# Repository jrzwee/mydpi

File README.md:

# mydpi
OpenSource debugger and programmer for ATmega and ATtiny microcontrollers from Microchip.

## Usage
+ Connect the myDPI to your computer, it should be recognised automatically. 
+ In Atmel Studio choose the myDPI debugger.
+ Set brakepoints, start debugging.

The connection to the device is realised with a Wurth Electronics [REDFIT](https://www.we-online.com/web/en/electronic_components/produkte_pb/produktinnovationen/redfit.php)
connector.

## Compatible Microcontrollers
+ ATtiny20x/40x/80x/160x
+ ATtiny21x/41x/81x/161x/321x
+ ATmega80x/160x/320x/480x

## Manufacture PCB
Click the logo to preview the order "**Push to Aisler**":

If you like this project, feel free to support me 😇

## License
[CERN-OHL-S](https://ohwr.org/cern_ohl_s_v2.pdf)

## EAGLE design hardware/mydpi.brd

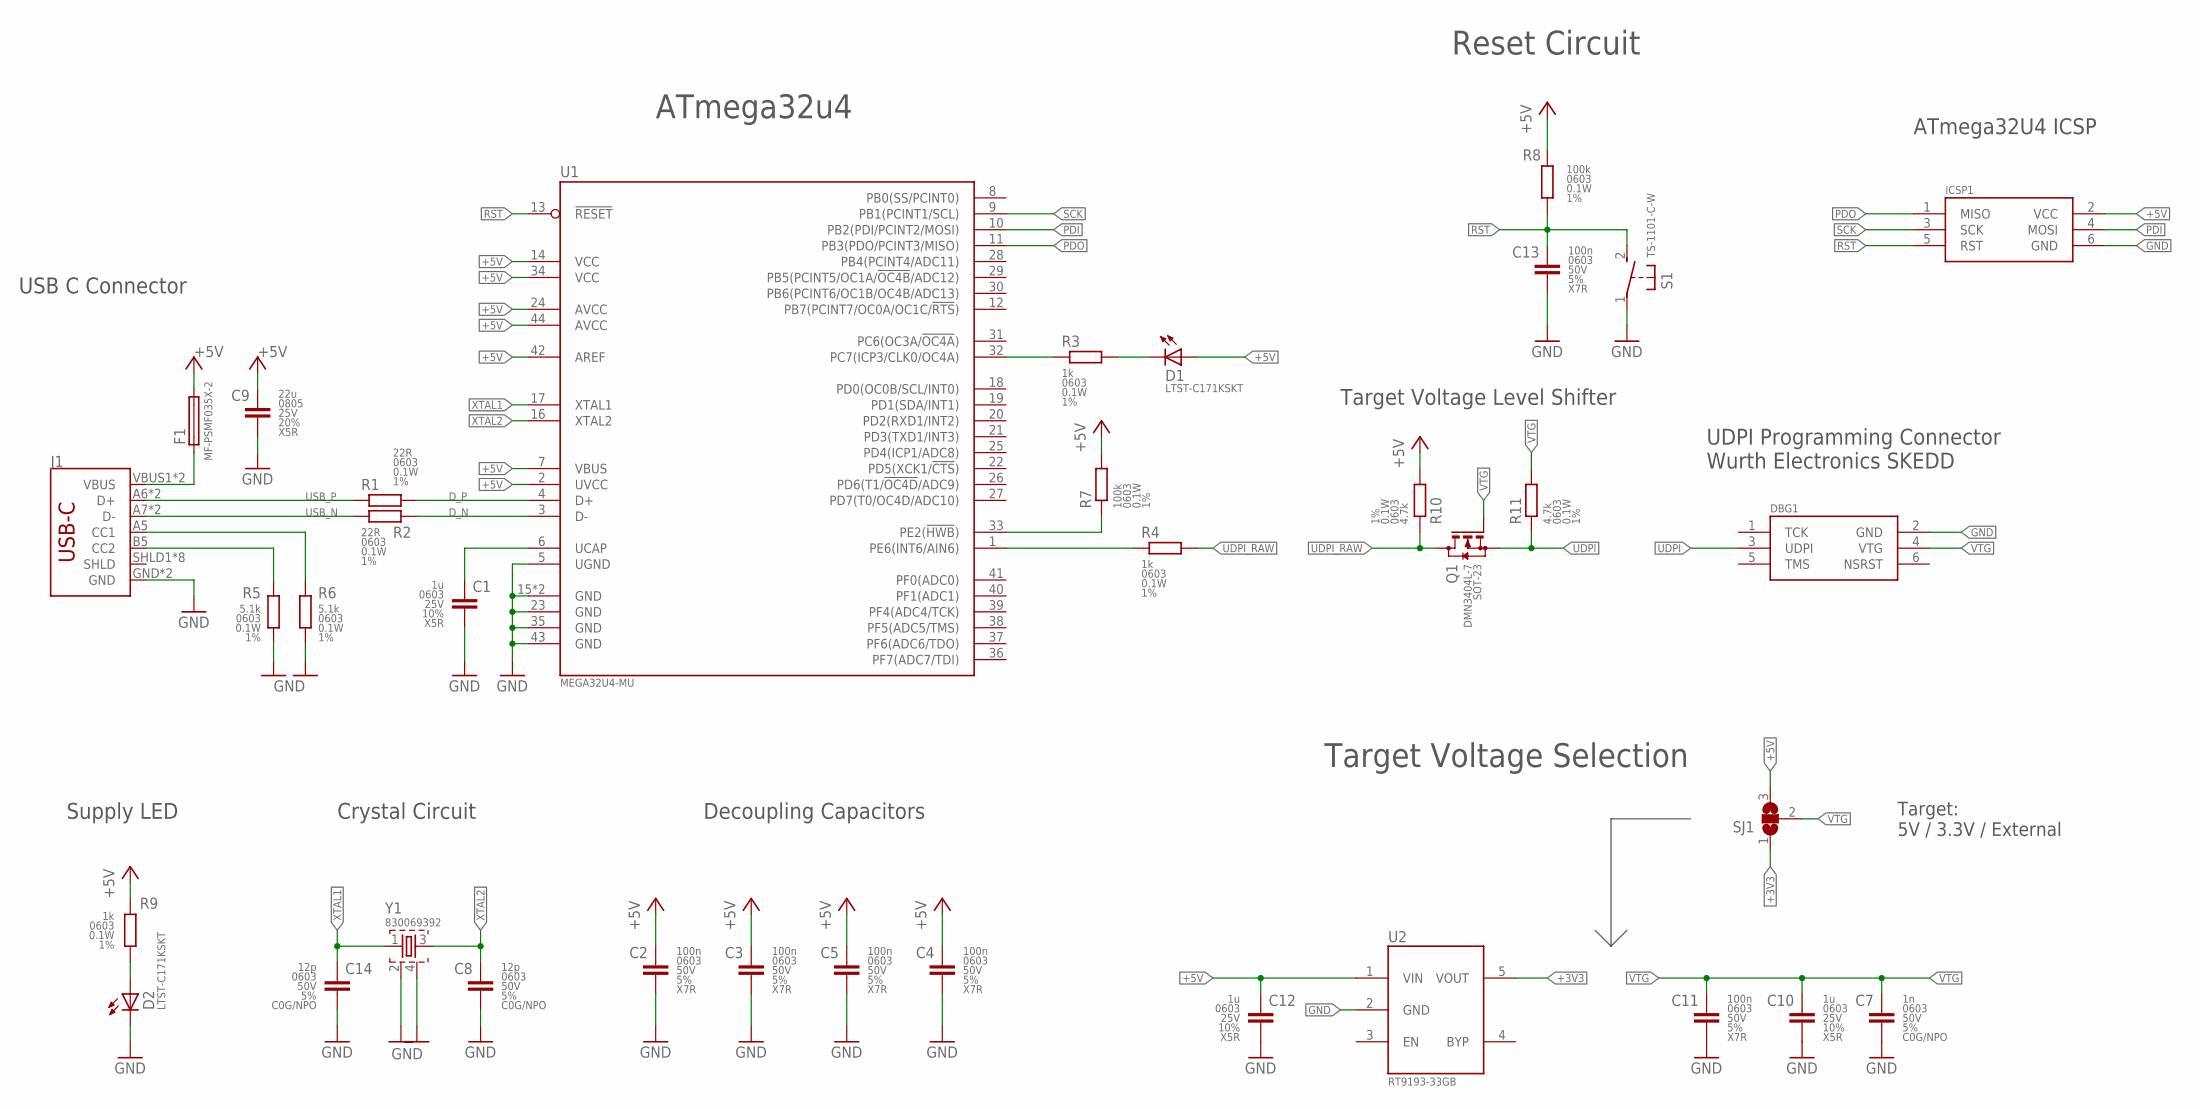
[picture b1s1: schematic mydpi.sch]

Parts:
C1, C10, C12: 1u; C0603
C2, C3, C4, C5, C11, C13: 100n; C0603
C7: 1n; C0603
C8, C14: 12p; C0603
C9: 22u; C0805
D1, D2: LTST-C171KSKT; CHIPLED_0805
DBG1: AVR-UPDI-6-SKEDD; 490107670612_DEBUGGING
F1: MF-PSMF035X-2; F0805
ICSP1: AVR-ISP-SMD; AVRISP-1.27-SMD
J1: USB_C2-LAYER; USB-C-16P
Q1: DMN3404L; SOT23
R1, R2: 22R; R0603
R3, R4, R9: 1k; R0603
R5, R6: 5.1k; R0603
R7, R8: 100k; R0603
R10, R11: 4.7k; R0603
S1: TS-1101-C-W; SPST-6X3.6
SJ1: SJ2W; SJ_2
U1: MEGA32U4-MU; TQFN44_7MM
U2: RT9193-33GB; SOT23-5
Y1: 830069392; WE-XTAL_CFPX-218

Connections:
+3V3: SJ1.1, U2.5 (VOUT)
+5V: C2.1, C3.1, C4.1, C5.1, C9.1, C12.1, D1.A, F1.2, ICSP1.2 (VCC), R7.2, R8.2, R9.1, R10.2, SJ1.3, U1.2 (UVCC), U1.7 (VBUS), U1.14 (VCC), U1.24 (AVCC), U1.34 (VCC), U1.42 (AREF), U1.44 (AVCC), U2.1 (VIN)
D_N: R2.2, U1.3 (D-)
D_P: R1.2, U1.4 (D+)
GND: C1.2, C2.2, C3.2, C4.2, C5.2, C7.2, C8.2, C9.2, C10.2, C11.2, C12.2, C13.2, C14.2, D2.C, DBG1.2 (GND), ICSP1.6 (GND), J1.GND, J1.GND2 (GND), R5.1, R6.1, S1.1, U1.5 (UGND), U1.15 (GND), U1.23 (GND), U1.35 (GND), U1.43 (GND), U1.EXP (GND), U2.2 (GND), Y1.2, Y1.4
unnamed: R3.1, U1.32 (PC7(ICP3/CLK0/OC4A))
unnamed: D1.C, R3.2
unnamed: J1.B5 (CC2), R5.2
unnamed: J1.A5 (CC1), R6.2
unnamed: R7.1, U1.33 (PE2(!HWB!))
unnamed: C1.1, U1.6 (UCAP)
unnamed: D2.A, R9.2
unnamed: F1.1, J1.VBUS1 (VBUS), J1.VBUS2 (VBUS)
PDI: ICSP1.4 (MOSI), U1.10 (PB2(PDI/PCINT2/MOSI))
PDO: ICSP1.1 (MISO), U1.11 (PB3(PDO/PCINT3/MISO))
PE6: R4.1, U1.1 (PE6(INT6/AIN6))
RST: C13.1, ICSP1.5 (RST), R8.1, S1.2 (S), U1.13 (!RESET!)
SCK: ICSP1.3 (SCK), U1.9 (PB1(PCINT1/SCL))
UDPI: DBG1.3 (UDPI), Q1.2 (S), R11.1
UDPI_RAW: Q1.3 (D), R4.2, R10.1
USB_N: J1.A7 (D-), J1.B7 (D-), R2.1
USB_P: J1.A6 (D+), J1.B6 (D+), R1.1
VTG: C7.1, C10.1, C11.1, DBG1.4 (VTG), Q1.1 (G), R11.2, SJ1.2
XTAL1: C14.1, U1.17 (XTAL1), Y1.1
XTAL2: C8.1, U1.16 (XTAL2), Y1.3

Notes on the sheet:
Target: 5V / 3.3V / External
Target Voltage Selection
ATmega32U4 ICSP
Reset Circuit
UDPI Programming Connector Wurth Electronics SKEDD
Target Voltage Level Shifter
ATmega32u4
Crystal Circuit
Supply LED
Decoupling Capacitors
USB C Connector

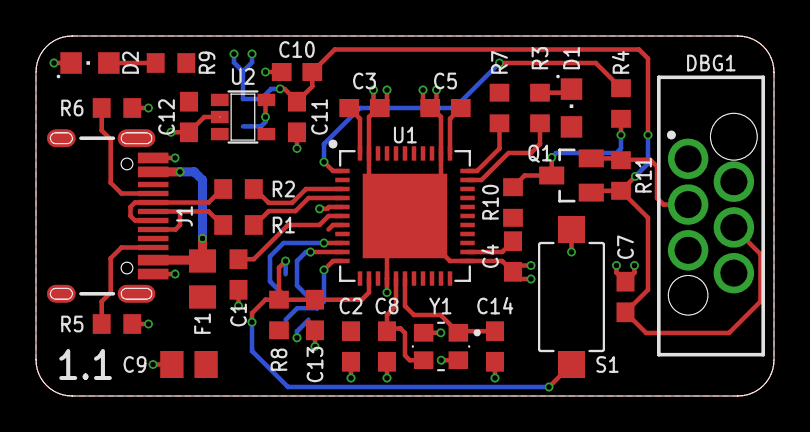
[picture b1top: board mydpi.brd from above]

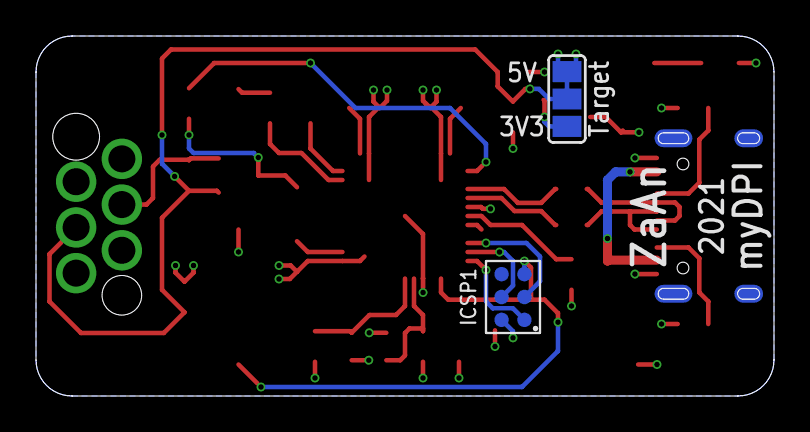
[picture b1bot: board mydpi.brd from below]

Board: 2 copper layers, 41.0 x 20.0 mm, 36 parts (2 on the bottom side), 25 nets.

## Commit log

2019-11-12 Schematic and board files generated
2019-11-12 Added supply voltage
2020-01-26 CC resistors added
2020-01-26 Placement LDO, Caps
2020-01-26 Crystal Added
2020-01-28 Added Reset Switch
2020-02-02 Button and Fuse added
2020-02-07 LDO added
2020-02-07 Minor placement change
2020-02-07 Minor changes placement
2020-02-07 Bugfixes in used libraries
2020-02-12 Updated Libraries
2020-03-08 Finished level shifter
2020-03-11 Added pullup resistors for level shifting
2020-03-17 Routing Pullup Resistors
2020-03-25 Changed silkscreen revision number
2020-04-23 Added GNU General Public License v3.0
2020-04-23 Restructure folders and added renders of PCB
2020-04-23 Added standard folder name
2020-04-23 Fitted renders for readme
2020-10-02 Corrected Vias to 0.3mm, Generated BOM
2021-01-24 Silkscreen size shrink to 0.81
2021-01-24 Update LICENSE
